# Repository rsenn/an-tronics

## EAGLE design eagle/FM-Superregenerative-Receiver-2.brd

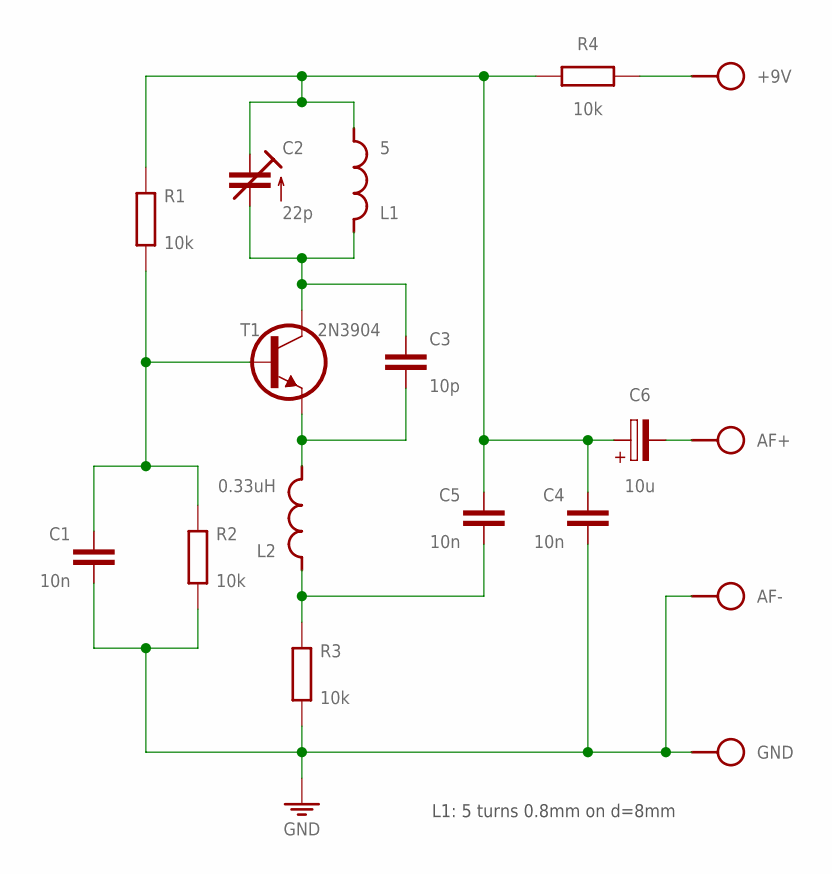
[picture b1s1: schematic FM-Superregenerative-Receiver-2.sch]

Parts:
+9V: SPAD
AF+: SPAD
AF-: SPAD
C1, C4, C5: 10n; C050-020X036/V
C2: 22p; TRIM-2222-808
C3: 10p; C050-020X036/V
C6: 10u; E2,5-3
GND: SPAD
L1: 5; L-04-5/5V-X
L2: 0.33uH; L-02/7V
R1, R2, R3: 10k; 0204/10
R4: 10k; 0204/7
T1: 2N3904; TO92

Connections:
GND: AF-.1, C1.2, C4.2, GND.1, R2.1, R3.1
unnamed: C1.1, R1.1, R2.2, T1.2 (B)
unnamed: AF+.1, C6.-
unnamed: C5.2, L2.2, R3.2
unnamed: C3.2, L2.1, T1.1 (E)
unnamed: C2.2 (A), C3.1, L1.2, T1.3 (C)
unnamed: +9V.1, R4.1
unnamed: C2.1 (E), C2.3 (E), C4.1, C5.1, C6.+, L1.1, R1.2, R4.2

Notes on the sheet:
L1: 5 turns 0.8mm on d=8mm

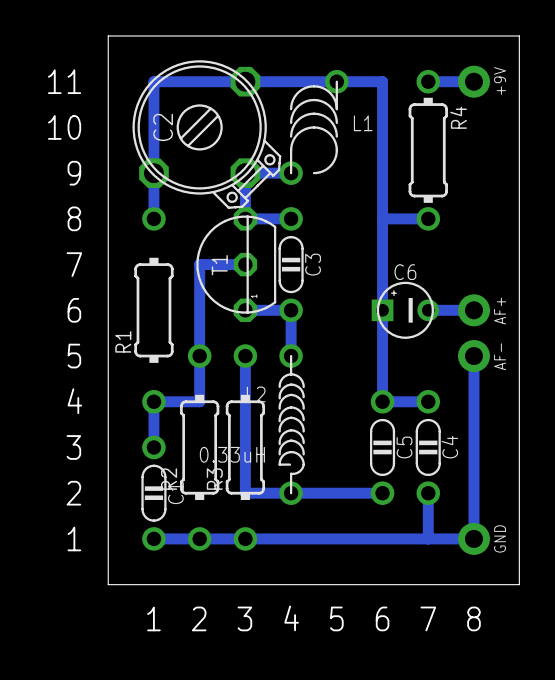
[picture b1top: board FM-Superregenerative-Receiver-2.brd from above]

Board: 2 copper layers, 22.8 x 30.5 mm, 17 parts (0 on the bottom side), 8 nets.

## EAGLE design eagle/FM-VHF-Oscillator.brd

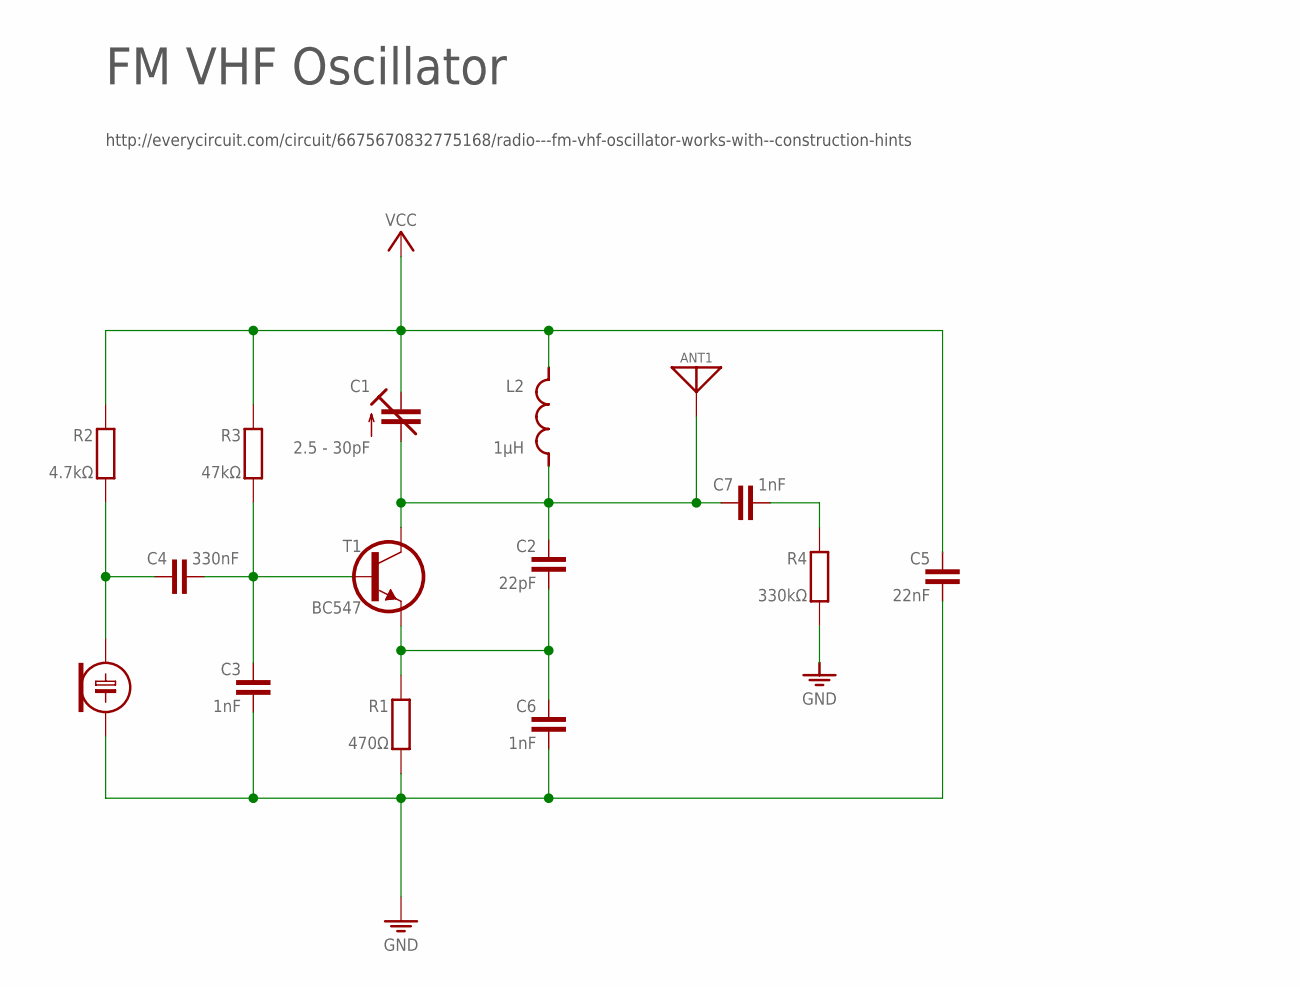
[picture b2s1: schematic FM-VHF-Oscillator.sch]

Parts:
ANT1: ANT; SPAD
C1: 2.5 - 30pF; TRIM-2222-808
C2: 22pF; C025-015X024
C3: 1nF; C050-020X036/V
C4: 330nF; C050-024X044
C5: 22nF; C050-020X044/V
C6: 1nF; C050-020X036
C7: 1nF; C050-024X044
ECM: ECM-4
L2: 1μH; L-04/7V-X
R1: 470Ω; 0204/2V
R2: 4.7kΩ; 0202/7-V
R3: 47kΩ; 0202/7-V
R4: 330kΩ; 0202/5-V
S2: VCC_GNDPWR-R; PWR-R
T1: BC547; TO92-CBE

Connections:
GND: C3.2, C5.2, C6.2, ECM.2 (-), R1.2, R4.2, S2.1 (GND)
unnamed: C7.2, R4.1
unnamed: ANT1.1, C1.2 (A), C2.1, C7.1, L2.1, T1.C
unnamed: C2.2, C6.1, R1.1, T1.E
unnamed: C3.1, C4.2, R3.2, T1.B
unnamed: C4.1, ECM.1 (+), R2.2
VCC: C1.3 (E), C5.1, L2.2, R2.1, R3.1, S2.2 (VCC)

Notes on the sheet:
http://everycircuit.com/circuit/6675670832775168/radio---fm-vhf-oscillator-works-with--construction-hints
FM VHF Oscillator

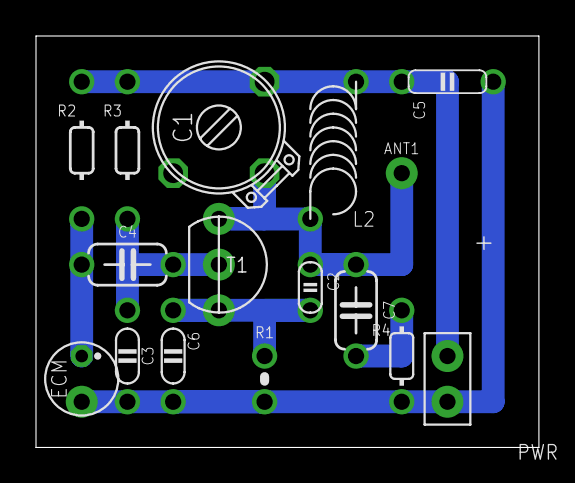
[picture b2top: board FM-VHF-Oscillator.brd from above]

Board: 2 copper layers, 27.9 x 22.9 mm, 16 parts (0 on the bottom side), 7 nets.

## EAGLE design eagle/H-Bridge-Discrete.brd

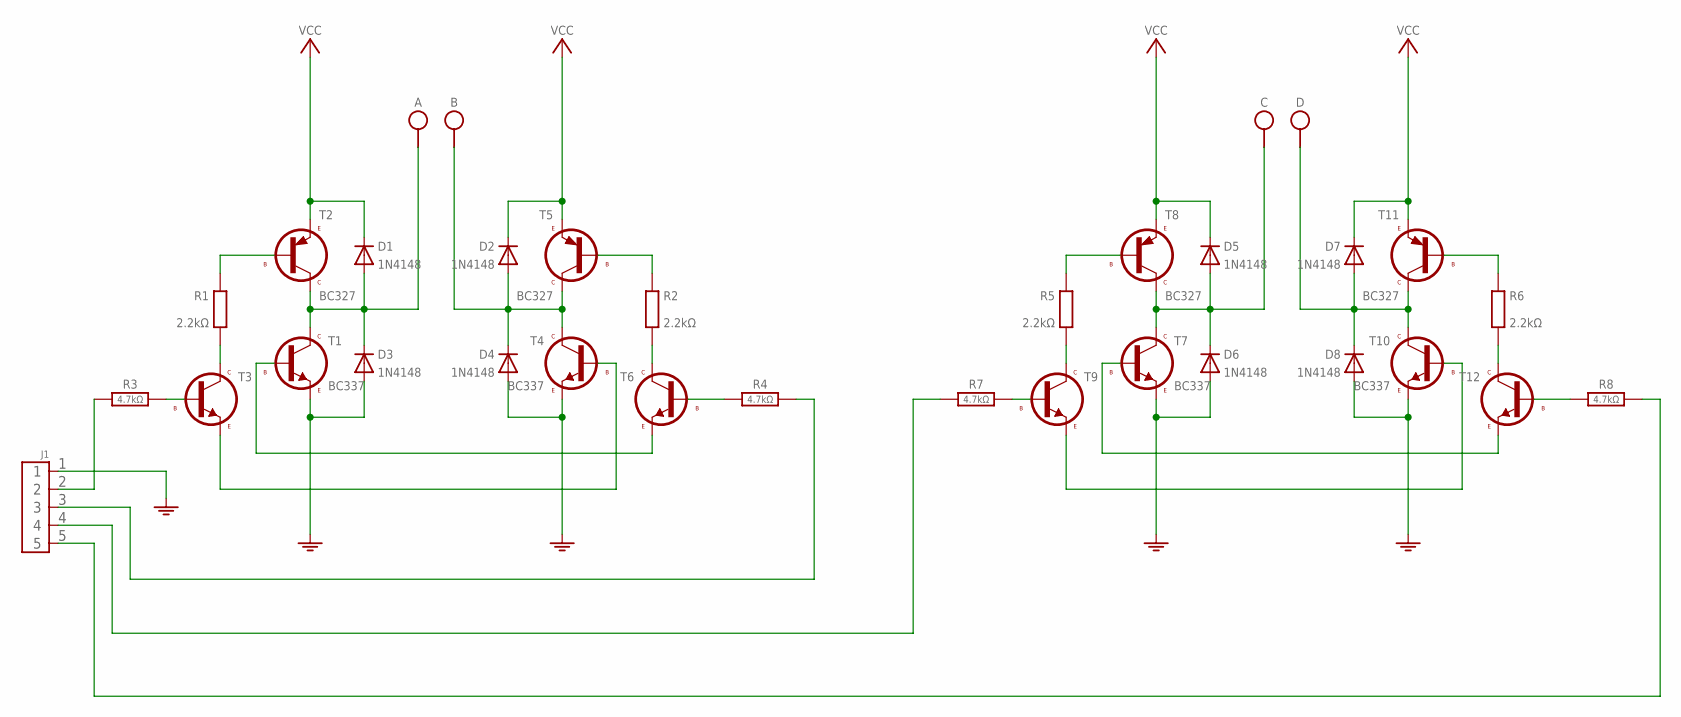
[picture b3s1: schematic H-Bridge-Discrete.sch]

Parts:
A: VPORT; SPAD
B: VPORT; SPAD
C: VPORT; SPAD
D: VPORT; SPAD
D1, D2, D3, D4, D5, D6, D7, D8: 1N4148; DO7-5
J1: CONN-5P-5P; CONN-5P
R1, R5, R6: 2.2kΩ; 0204/10
R2: 2.2kΩ; 0204/2
R3, R4, R7, R8: 4.7kΩ; 0204/10
S1: VCC_GND-508-L; PWR-508-L
T1, T4, T7, T10: BC337; TO92-CBE
T2, T5, T8, T11: BC327; TO92
T3, T6, T9, T12: BC547; TO92

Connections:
GND: D3.A, D4.A, D6.A, D8.A, J1.1, S1.1 (GND), T1.3 (E), T4.3 (E), T7.3 (E), T10.3 (E)
unnamed: R2.1 (2), T5.2 (B)
unnamed: R2.2 (1), T6.1 (C)
unnamed: T1.2 (B), T6.3 (E)
unnamed: R1.1 (2), T2.2 (B)
unnamed: R1.2 (1), T3.1 (C)
unnamed: T3.3 (E), T4.2 (B)
unnamed: B.1, D2.A, D4.C, T4.1 (C), T5.1 (C)
unnamed: A.1, D1.A, D3.C, T1.1 (C), T2.1 (C)
unnamed: R3.2, T3.2 (B)
unnamed: R4.1, T6.2 (B)
unnamed: J1.2, R3.1
unnamed: J1.3, R4.2
unnamed: R5.1 (2), T8.2 (B)
unnamed: R5.2 (1), T9.1 (C)
unnamed: T9.3 (E), T10.2 (B)
unnamed: C.1, D5.A, D6.C, T7.1 (C), T8.1 (C)
unnamed: R6.1 (2), T11.2 (B)
unnamed: R6.2 (1), T12.1 (C)
unnamed: T7.2 (B), T12.3 (E)
unnamed: D.1, D7.A, D8.C, T10.1 (C), T11.1 (C)
unnamed: R8.1, T12.2 (B)
unnamed: R7.2, T9.2 (B)
unnamed: J1.5, R8.2
unnamed: J1.4, R7.1
VCC: D1.C, D2.C, D5.C, D7.C, S1.2 (VCC), T2.3 (E), T5.3 (E), T8.3 (E), T11.3 (E)

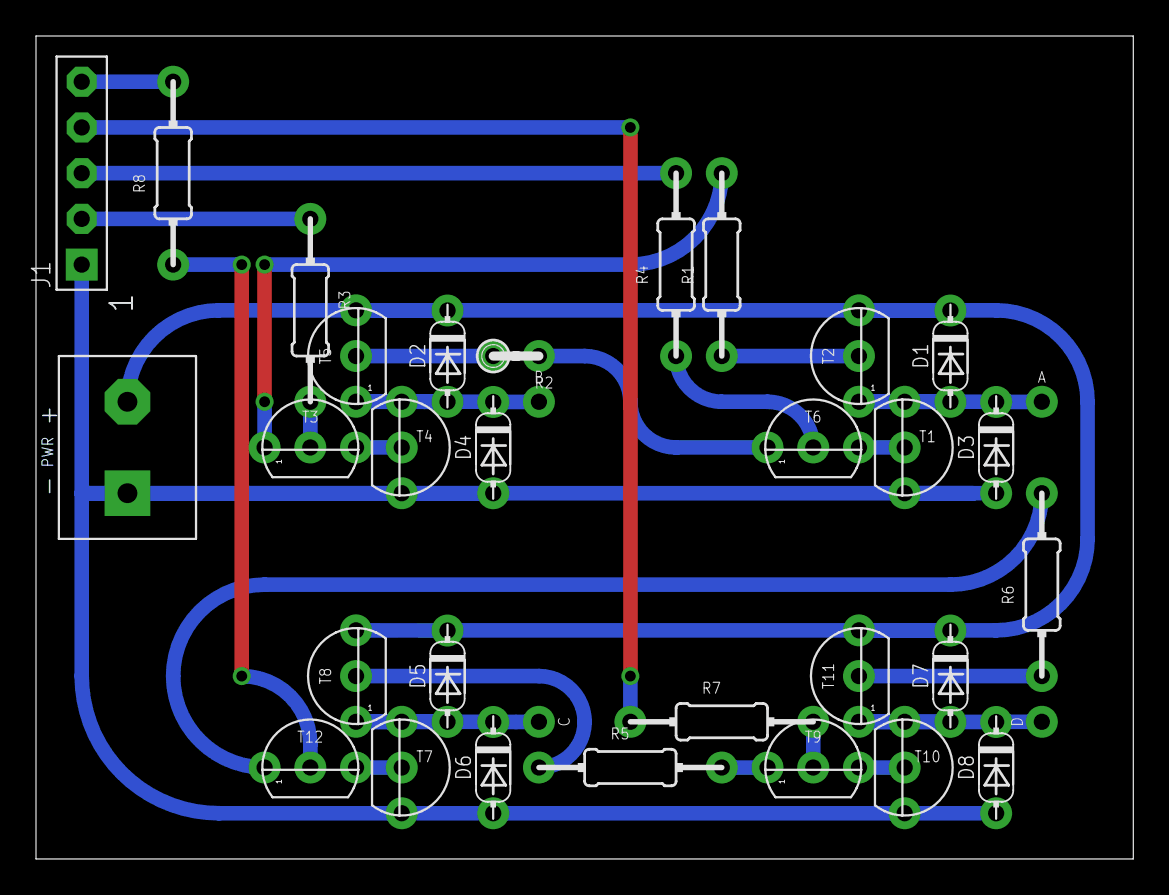
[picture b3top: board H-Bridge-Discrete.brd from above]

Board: 2 copper layers, 61.0 x 45.7 mm, 34 parts (0 on the bottom side), 26 nets.

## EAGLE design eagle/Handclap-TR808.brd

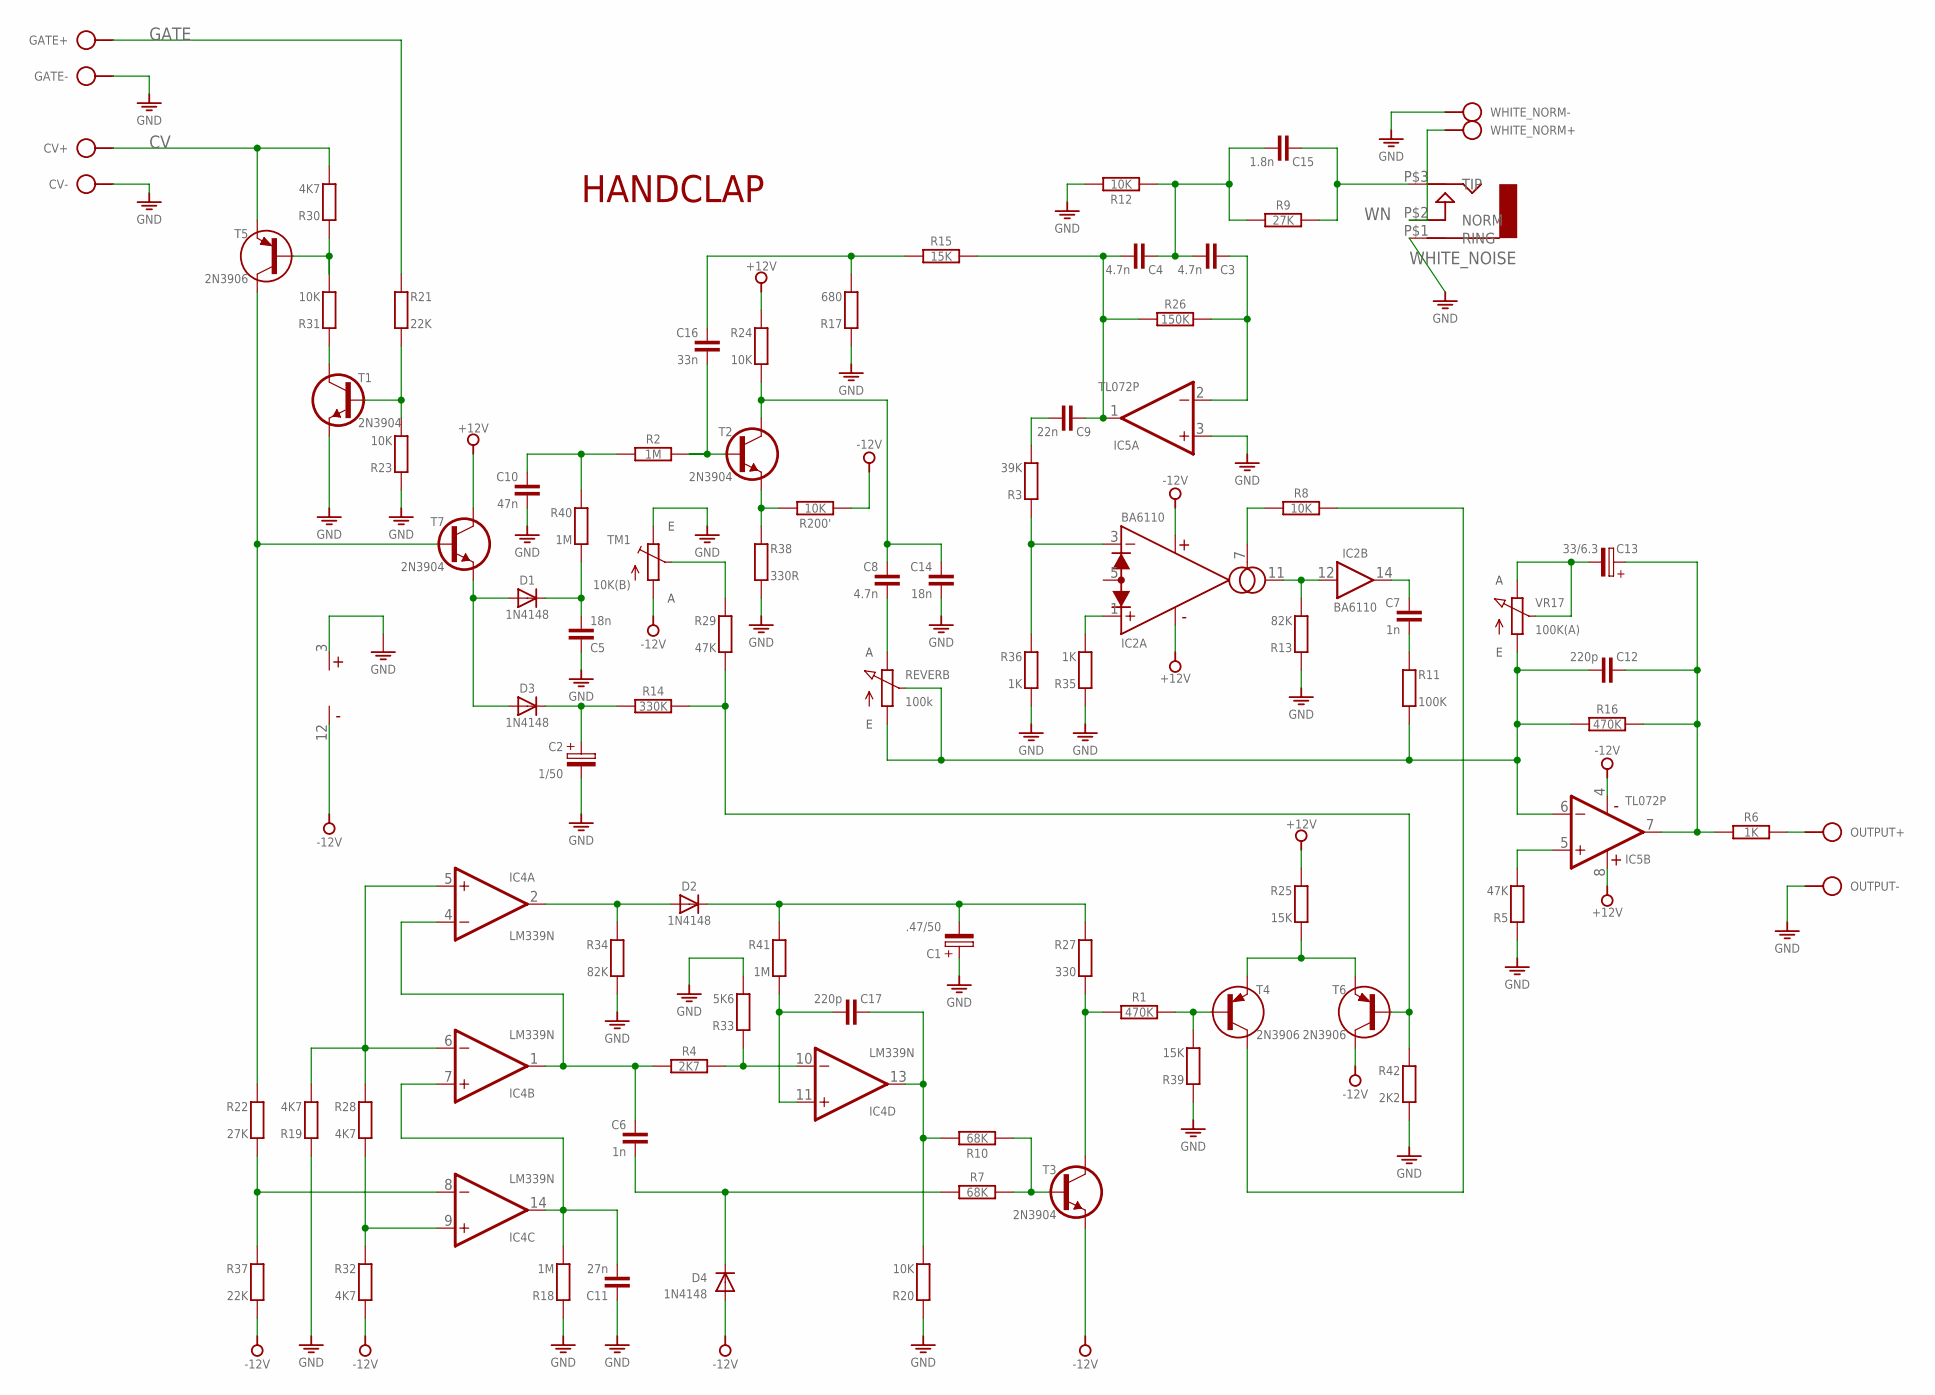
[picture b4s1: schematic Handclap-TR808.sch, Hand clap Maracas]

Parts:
C1: .47/50; E2,5-3/V
C2: 1/50; E2.5-4/V
C3, C4: 4.7n; C050-020X044
C5, C14: 18n; C050-020X044/V
C6, C7: 1n; C050-020X044/V
C8: 4.7n; C050-020X044/V
C9: 22n; C050-020X044
C10: 47n; C050-020X044/V
C11: 27n; C050-020X044/V
C12, C17: 220p; C050-020X044
C13: 33/6.3; E2,5-3
C15: 1.8n; C050-020X044
C16: 33n; C050-020X044/V
CV: SPAD+--+; SPAD-+
D1, D3: 1N4148; DO34-10
D2: 1N4148; DO34-2,5-A/V
D4: 1N4148; DO34-7V
GATE: SPAD+--+; SPAD-+
IC2: BA6110; DIL16
IC4: LM339N; DIL14
IC5: TL072P; DIL08
OUTPUT: SPAD+--+; SPAD-+
PWR1: -12V_GND_+12V-VCC-VEE; SPAD-PWR-+GND-
R1, R16: 470K; 0204/10
R2: 1M; 0204/10
R3: 39K; 0204/10-V
R4: 2K7; 0204/10
R5, R29: 47K; 0204/10-V
R6: 1K; 0204/10
R7, R10: 68K; 0204/10
R8, R12, R200': 10K; 0204/10
R9: 27K; 0204/10
R11: 100K; 0204/10-V
R13, R34: 82K; 0204/10-V
R14: 330K; 0204/10
R15: 15K; 0204/10
R17: 680; 0204/10-V
R18, R40, R41: 1M; 0204/10-V
R19, R28, R30, R32: 4K7; 0204/10-V
R20, R23, R24, R31: 10K; 0204/10-V
R21, R37: 22K; 0204/10-V
R22: 27K; 0204/10-V
R25, R39: 15K; 0204/10-V
R26: 150K; 0204/10
R27: 330; 0204/10-V
R33: 5K6; 0204/10-V
R35, R36: 1K; 0204/10-V
R38: 330R; 0204/10-V
R42: 2K2; 0204/10-V
REVERB: 100k; CONN-3P
T1, T2, T3, T7: 2N3904; TO92
T4, T5, T6: 2N3906; TO92
TM1: 10K(B); R-TRIM
VR17: 100K(A); CONN-3P
WHITE_NOISE: AUDIO-JACK; ERTHENVAR-JACK-90DEG
WHITE_NORM: SPAD+-+-; SPAD+-

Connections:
+12V: IC2.9 (V-), IC5.8 (V+), PWR1.VCC (+12V), R24.1, R25.1, T7.3 (C)
-12V: D4.A, IC2.15 (V+), IC4.12 (V-), IC5.4 (V-), PWR1.VEE (-12V), R32.2, R37.2, R200'.2, T3.1 (E), T6.3 (C), TM1.1 (A)
A_OUT: D2.A, IC4.2 (OUT), R34.1
B_OUT: C6.1, IC4.1 (OUT), IC4.4 (-IN), R4.2
CV: CV.2, R30.2, T5.1 (E)
C_OUT: C11.2, IC4.7 (+IN), IC4.14 (OUT), R18.2
D_OUT: C17.1, IC4.13 (OUT), R10.1, R20.2
GATE: GATE.2, R21.1
GND: C1.+, C2.-, C5.1, C10.2, C11.1, C14.2, CV.1, GATE.1, IC4.3 (V+), IC5.3 (+IN), OUTPUT.1, PWR1.GND, R5.1, R12.1, R13.1, R17.1, R18.1, R19.1, R20.1, R23.1, R33.2, R34.2, R35.1, R36.2, R38.2, R39.1, R42.2, T1.1 (E), TM1.3 (E), WHITE_NOISE.P$1 (RING), WHITE_NORM.1
unnamed: OUTPUT.2, R6.1
unnamed: WHITE_NOISE.P$2 (NORM), WHITE_NORM.2
unnamed: R31.1, T1.3 (C)
unnamed: R21.2, R23.2, T1.2 (B)
unnamed: C4.2, C9.1, IC5.1 (OUT), R15.1, R26.2
unnamed: R30.1, R31.2, T5.2 (B)
unnamed: C16.2, R2.1, T2.2 (B)
unnamed: C5.2, D1.C, R40.2
unnamed: R38.1, R200'.1, T2.1 (E)
unnamed: R22.1, T5.3 (C), T7.2 (B)
unnamed: D1.A, D3.A, T7.1 (E)
unnamed: C10.1, R2.2, R40.1
unnamed: C8.1, C14.1, R24.2, T2.3 (C)
unnamed: C2.+, D3.C, R14.2
unnamed: R14.1, R29.2, R42.1, T6.2 (B)
unnamed: R29.1, TM1.2 (S)
unnamed: C16.1, R15.2, R17.2
unnamed: C3.2, C4.1, C15.2, R9.2, R12.2
unnamed: C3.1, IC5.2 (-IN), R26.1
unnamed: C9.2, R3.2
unnamed: IC2.3 (-IN), R3.1, R36.1
unnamed: C8.2, REVERB.3 (E)
unnamed: IC2.1 (+IN), R35.2
unnamed: IC2.7 (AMP/BIAS), R8.1
unnamed: IC2.11 (OUT), IC2.12 (B_IN), R13.2
unnamed: C7.2, R11.1
unnamed: C7.1, IC2.14 (B_OUT)
unnamed: IC4.5 (+IN), IC4.6 (-IN), R19.2, R28.1
unnamed: C1.-, D2.C, R27.1, R41.1
unnamed: R1.1, R39.2, T4.2 (B)
unnamed: R25.2, T4.1 (E), T6.1 (E)
unnamed: R8.2, T4.3 (C)
unnamed: R1.2, R27.2, T3.3 (C)
unnamed: IC4.9 (+IN), R28.2, R32.1
unnamed: C17.2, IC4.11 (+IN), R41.2
unnamed: IC4.10 (-IN), R4.1, R33.1
unnamed: IC4.8 (-IN), R22.2, R37.1
unnamed: R7.1, R10.2, T3.2 (B)
unnamed: C6.2, D4.C, R7.2
unnamed: IC5.5 (+IN), R5.2
unnamed: C12.2, IC5.6 (-IN), R11.2, R16.2, REVERB.1 (A), REVERB.2 (S), VR17.1 (A)
unnamed: C13.-, VR17.2 (S), VR17.3 (E)
unnamed: C12.1, C13.+, IC5.7 (OUT), R6.2, R16.1
WN: C15.1, R9.1, WHITE_NOISE.P$3 (TIP)

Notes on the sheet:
HANDCLAP

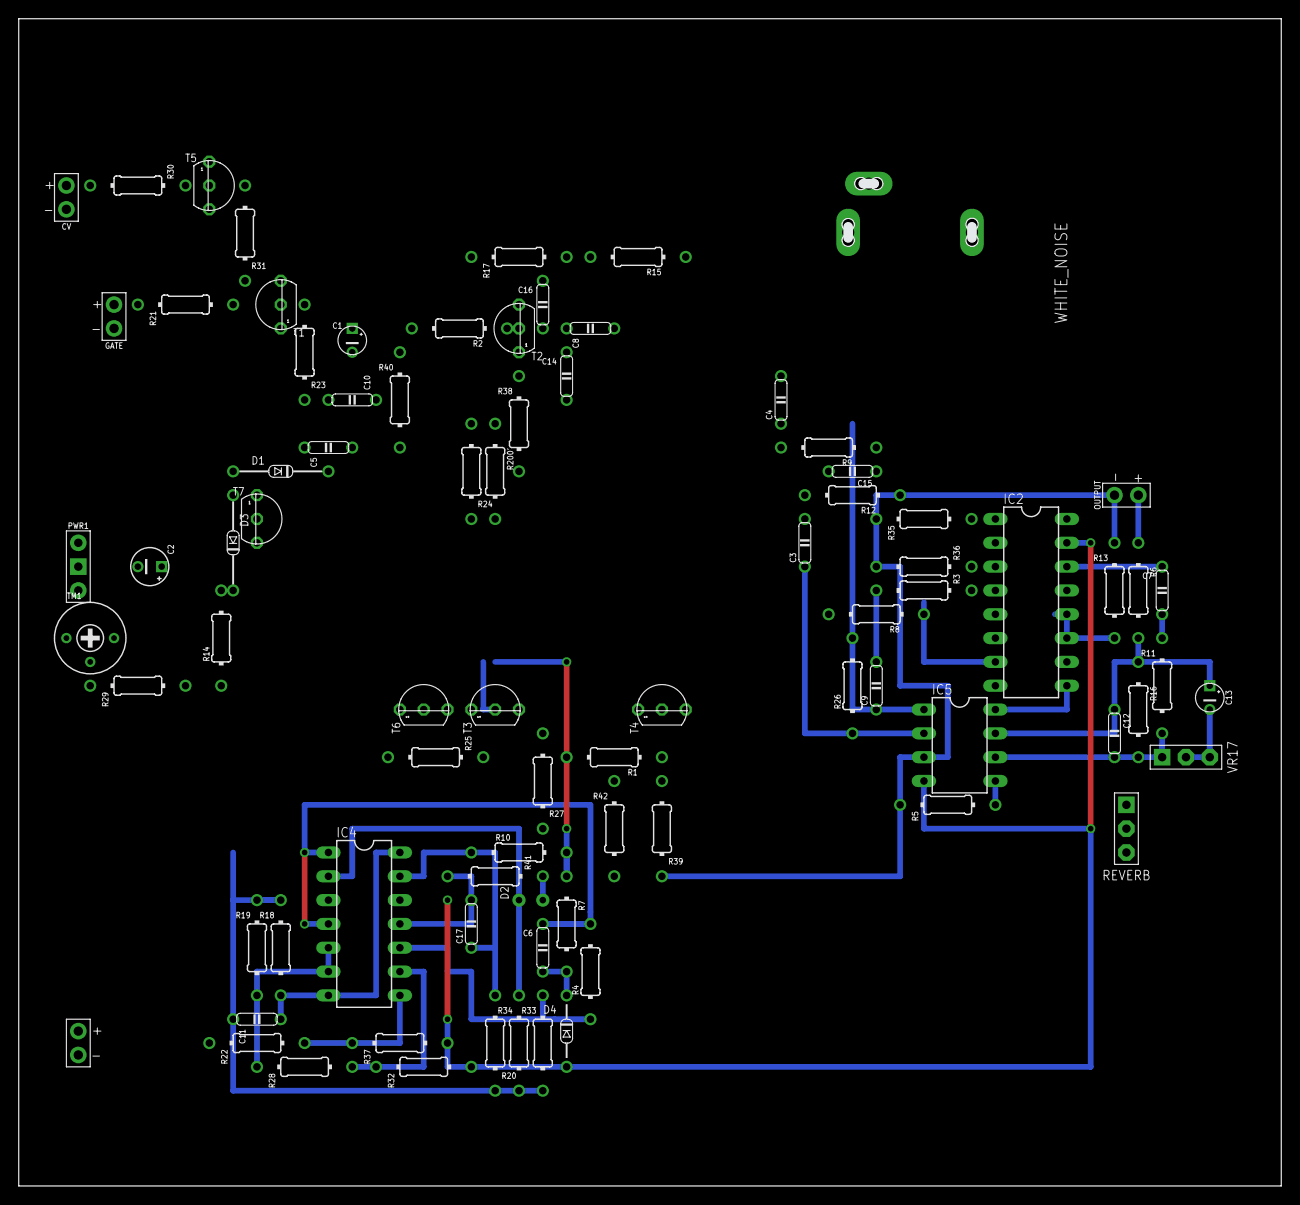
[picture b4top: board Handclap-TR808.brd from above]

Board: 2 copper layers, 134.6 x 124.5 mm, 83 parts (0 on the bottom side), 53 nets.

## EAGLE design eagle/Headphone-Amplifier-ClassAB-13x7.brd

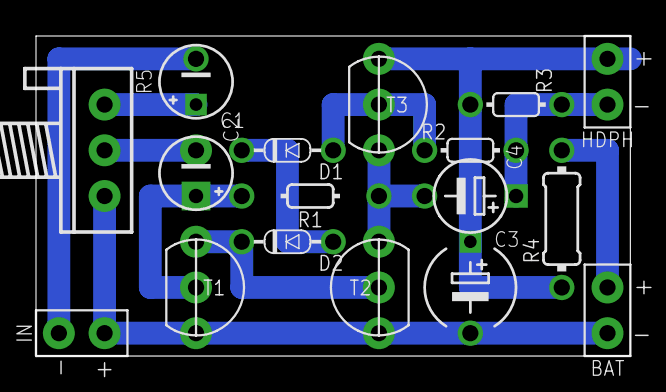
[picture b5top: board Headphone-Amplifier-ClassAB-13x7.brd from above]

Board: 2 copper layers, 33.0 x 17.8 mm, 17 parts (0 on the bottom side), 12 nets.

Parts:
BAT: SPAD+-+-; SPAD+-
C1: 4.7μF; E2.5-4/V
C2: 4.7μF; E2,5-4
C3: 100-1000μF; E5-5/V
C4: 220μF; E5-4
D1, D2: 1N4148; DO34-5
HDPH: SPAD+-+-; SPAD+-
IN: SPAD+-+-; SPAD+-
R1: 100kΩ; 0202/7
R2: 330Ω; 0202/5
R3: 100Ω; 0202/5-V
R4: 22Ω; 0204/7
R5: 100kΩ; POT
T1, T3: BC547; TO92-CBE
T2: BC557; TO92-CBE

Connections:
AF: D2.C, T1.C, T2.B
GND: BAT.1, C3.-, IN.2, R5.3, T1.E, T2.C
unnamed: D1.A, R2.1, T3.B
unnamed: D1.C, D2.A
unnamed: C4.-, R1.2, T2.E, T3.E
unnamed: C1.+, R5.1
unnamed: C2.-, R5.2
unnamed: C2.+, R1.1, T1.B
unnamed: C4.+, HDPH.1, R2.2, R3.1
unnamed: C1.-, IN.1
V+: BAT.2, R4.2
VCC: C3.+, HDPH.2, R3.2, R4.1, T3.C

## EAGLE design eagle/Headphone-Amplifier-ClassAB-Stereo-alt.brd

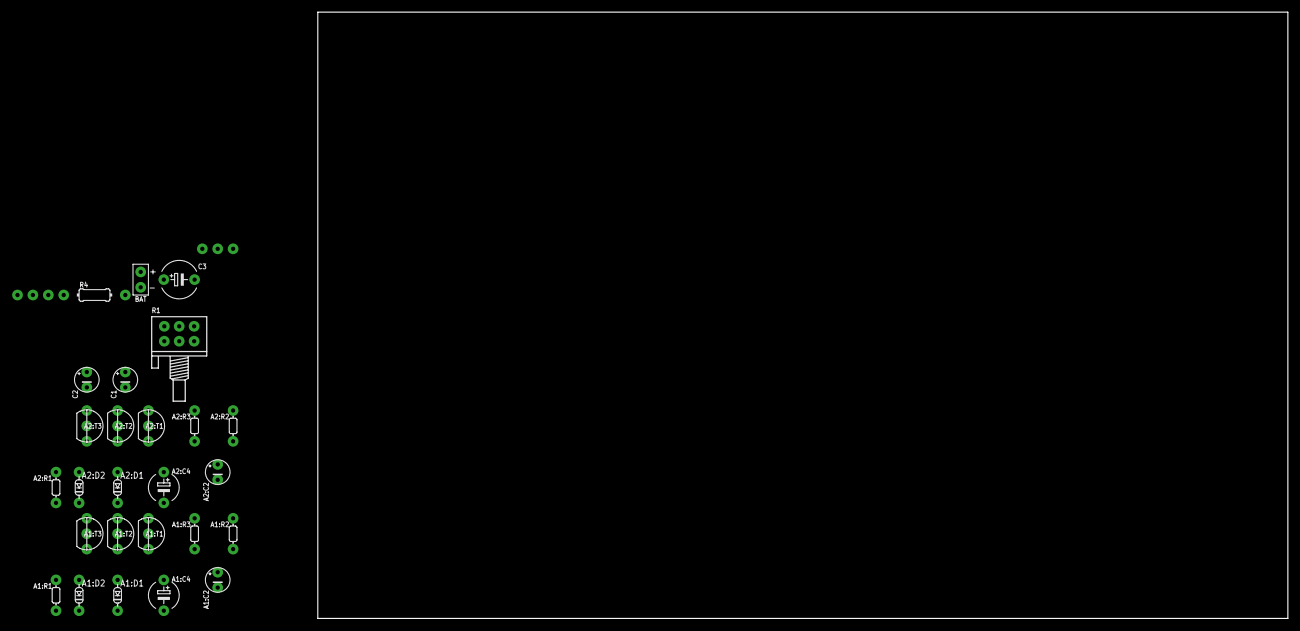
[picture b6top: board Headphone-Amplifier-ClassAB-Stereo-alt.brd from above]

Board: 2 copper layers, 160.0 x 100.0 mm, 28 parts (0 on the bottom side), 21 nets, no tracks yet.

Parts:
A1:C2, A2:C2: 4.7μF; E2,5-4
A1:C4, A2:C4: 220μF; E5-5/V
A1:D1, A1:D2, A2:D1, A2:D2: 1N4148; DO34-5V
A1:R1, A2:R1: 100kΩ; 0202/5-V
A1:R2, A2:R2: 330; 0202/5-V
A1:R3, A2:R3: 100; 0202/5-V
A1:T1, A1:T3, A2:T1, A2:T3: BC547; TO92-CBE
A1:T2, A2:T2: BC557; TO92-CBE
BAT: SPAD+-+-; SPAD+-
C1, C2: 4.7μF; E2,5-4
C3: 100-1000μF; E5-6
IN: SAUDIO; SPAD-3
OUT: SAUDIO; SPAD-3
R1: POT-STEREO; POT-STEREO-2X3
R4: 22Ω; 0204/10

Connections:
+3V: BAT.2, R4.2
A1:N$1: A1:D1.A, A1:R2.1, A1:T3.B
A1:N$2: A1:D2.C, A1:T1.C, A1:T2.B
A1:N$3: A1:D1.C, A1:D2.A
A1:N$4: A1:C4.-, A1:R1.2, A1:T2.E, A1:T3.E
A1:N$7: A1:C2.+, A1:R1.1, A1:T1.B
A2:N$1: A2:D1.A, A2:R2.1, A2:T3.B
A2:N$2: A2:D2.C, A2:T1.C, A2:T2.B
A2:N$3: A2:D1.C, A2:D2.A
A2:N$4: A2:C4.-, A2:R1.2, A2:T2.E, A2:T3.E
A2:N$7: A2:C2.+, A2:R1.1, A2:T1.B
GND: A1:T1.E, A1:T2.C, A2:T1.E, A2:T2.C, BAT.1, C3.-, IN.2, OUT.2, R1.1-E, R1.2-E
unnamed: A1:R3.1, A1:T3.C, A2:R3.1, A2:T3.C, C3.+, R4.1
unnamed: A1:C4.+, A1:R2.2, A1:R3.2, OUT.1
unnamed: C2.-, IN.3
unnamed: C2.+, R1.2-A
unnamed: C1.+, R1.1-A
unnamed: A1:C2.-, R1.1-S
unnamed: A2:C2.-, R1.2-S
unnamed: A2:C4.+, A2:R2.2, A2:R3.2, OUT.3
unnamed: C1.-, IN.1
